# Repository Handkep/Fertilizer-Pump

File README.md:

# Automatic Fertilizer Dispenser

The fertilizer dispenser automatically doses fertilizer concentrates or stock solutions using one or more peristaltic pumps. The amount dispensed depends on the selected recipe and the intended irrigation water volume. After dosing, the pump and outlet tubing are flushed with water to help prevent salt deposits.

**Project status:** In development. The Peristaltic pump is currently in the prototyping phase. PCB design is in progress. The user interface and display are still to be determined.

## How It Works

Each recipe specifies a dose in ml per liter of irrigation water for each fertilizer. The required amount is calculated as follows:

```text
Fertilizer volume [ml] = Water volume [L] × Dose [ml/L]

Example: 10 L of water × 5 ml/L = 50 ml of fertilizer
```

A recipe can contain multiple fertilizers. Each fertilizer has its own separate channel, and the fertilizers are mixed only in the watering can. In the future, the device may support mixing fertilizers, after the pumps, to have a single outlet for the mixed solution. 

## Operation

The planned interface consists of a display and a rotary encoder with a push button:

1. **Set the water volume:** Turn the knob. Each detent increases the selected volume by 1 L.
2. **Confirm the volume:** Press the knob to proceed to recipe selection.
3. **Select a recipe:** Turn the knob to choose the desired recipe.
4. **Start dosing:** Press the knob again to dispense the fertilizer.

the further interface planning is still in progress. The display type has not yet been selected.

## Hardware

| Component | Planned configuration |
| --- | --- |
| Controller | ESP32-S3 |
| Channels | Four positions, initially only two populated with TMC2209 modules |
| Motor drivers | Plug-in TMC2209 StepStick modules |
| Driver control | STEP/DIR/EN and UART |
| Pumps | Custom stepper-driven peristaltic pumps, designed in Onshape |
| Motors | NEMA17 stepper motors |
| User interface | Rotary encoder with push button and a display |
| Display | To be selected: a small OLED or another display type; no seven-segment display |
| Calibration | Individual steps-per-ml calibration for each pump |

## Power and USB

### V1

- Motor and solenoid valve operation requires USB-C PD or a separate 12 V power supply.
- USB-C provides data connectivity and firmware flashing.
- USB alone is intended to power the control electronics, including the ESP32-S3 and user interface. Motors and solenoid valves remain inactive without the 12 V supply. The 12 V supply should not be required for firmware flashing.
- USB Power Delivery is included in V1.

## Fluid Path and Flushing

Each fertilizer channel has a selector valve upstream of the pump:

```mermaid
flowchart LR
    fertilizer["Fertilizer concentrate<br/>or stock solution"] -->|Dosing| valve{"Selector valve"}
    water["Flush water"] -->|Flushing| valve
    valve --> pump(["Peristaltic pump"])
    pump -->|Outlet tubing| can["Watering can"]

    classDef fertilizerStyle fill:#dcfce7,stroke:#15803d,color:#14532d,stroke-width:2px;
    classDef waterStyle fill:#dbeafe,stroke:#2563eb,color:#1e3a8a,stroke-width:2px;
    classDef hardwareStyle fill:#f1f5f9,stroke:#64748b,color:#0f172a,stroke-width:2px;
    classDef outputStyle fill:#fef3c7,stroke:#d97706,color:#78350f,stroke-width:2px;

    class fertilizer fertilizerStyle;
    class water waterStyle;
    class valve,pump hardwareStyle;
    class can outputStyle;
    linkStyle 0 stroke:#15803d,stroke-width:2px;
    linkStyle 1 stroke:#2563eb,stroke-width:2px;
```

V1 will initially use an inexpensive electrically operated two-position solenoid selector valve.

After dosing, the valve switches to water to flush the pump and outlet tubing. The flushing water also flows into the watering can.

The additional flushing water is not included in the fertilizer dose calculation. For the intended use, this extra volume is considered small relative to the uncertainty of measuring the water volume in a watering can.

### Planned for V2

- "peristaltic" selector valve built out of a servo and a 3D-printed part.
    - The servo connector will already be included on the V1 PCB to simplify this future upgrade.

## Development Status

The operating concept, four channel positions with two initially populated motor drivers, and separate fertilizer paths have been defined.

Practical testing is still pending. The display has not yet been selected.

## Future Possibilities

- Release with open-source firmware and noncommercial hardware designs
- A PCB kit or complete DIY kit
- Accompanying project documentation on YouTube

## License

Copyright (c) 2026 Paulus Handke.

- Original firmware: [GPL-3.0-only](LICENSES/GPL-3.0-only.txt), including commercial use and distribution under the GPL.
- Original hardware design files and documentation: [CC BY-NC-SA 4.0](LICENSES/CC-BY-NC-SA-4.0.txt), covering copyright and similar rights.

**Commercial use of the licensed hardware files or documentation, including manufacturing from those files for sale, requires prior written permission**, except as permitted in [LICENSE](LICENSE).
Additional permissions cover paid fabrication for noncommercial end use and freely accessible, monetized project presentations; see [LICENSE](LICENSE) for their scope and conditions.
Third-party material retains its own licenses; see [THIRD_PARTY_NOTICES.md](THIRD_PARTY_NOTICES.md).
For commercial permission, contact Paulus Handke through [repository issues](https://github.com/Handkep/Fertilizer-Pump/issues). An unanswered request is not permission.

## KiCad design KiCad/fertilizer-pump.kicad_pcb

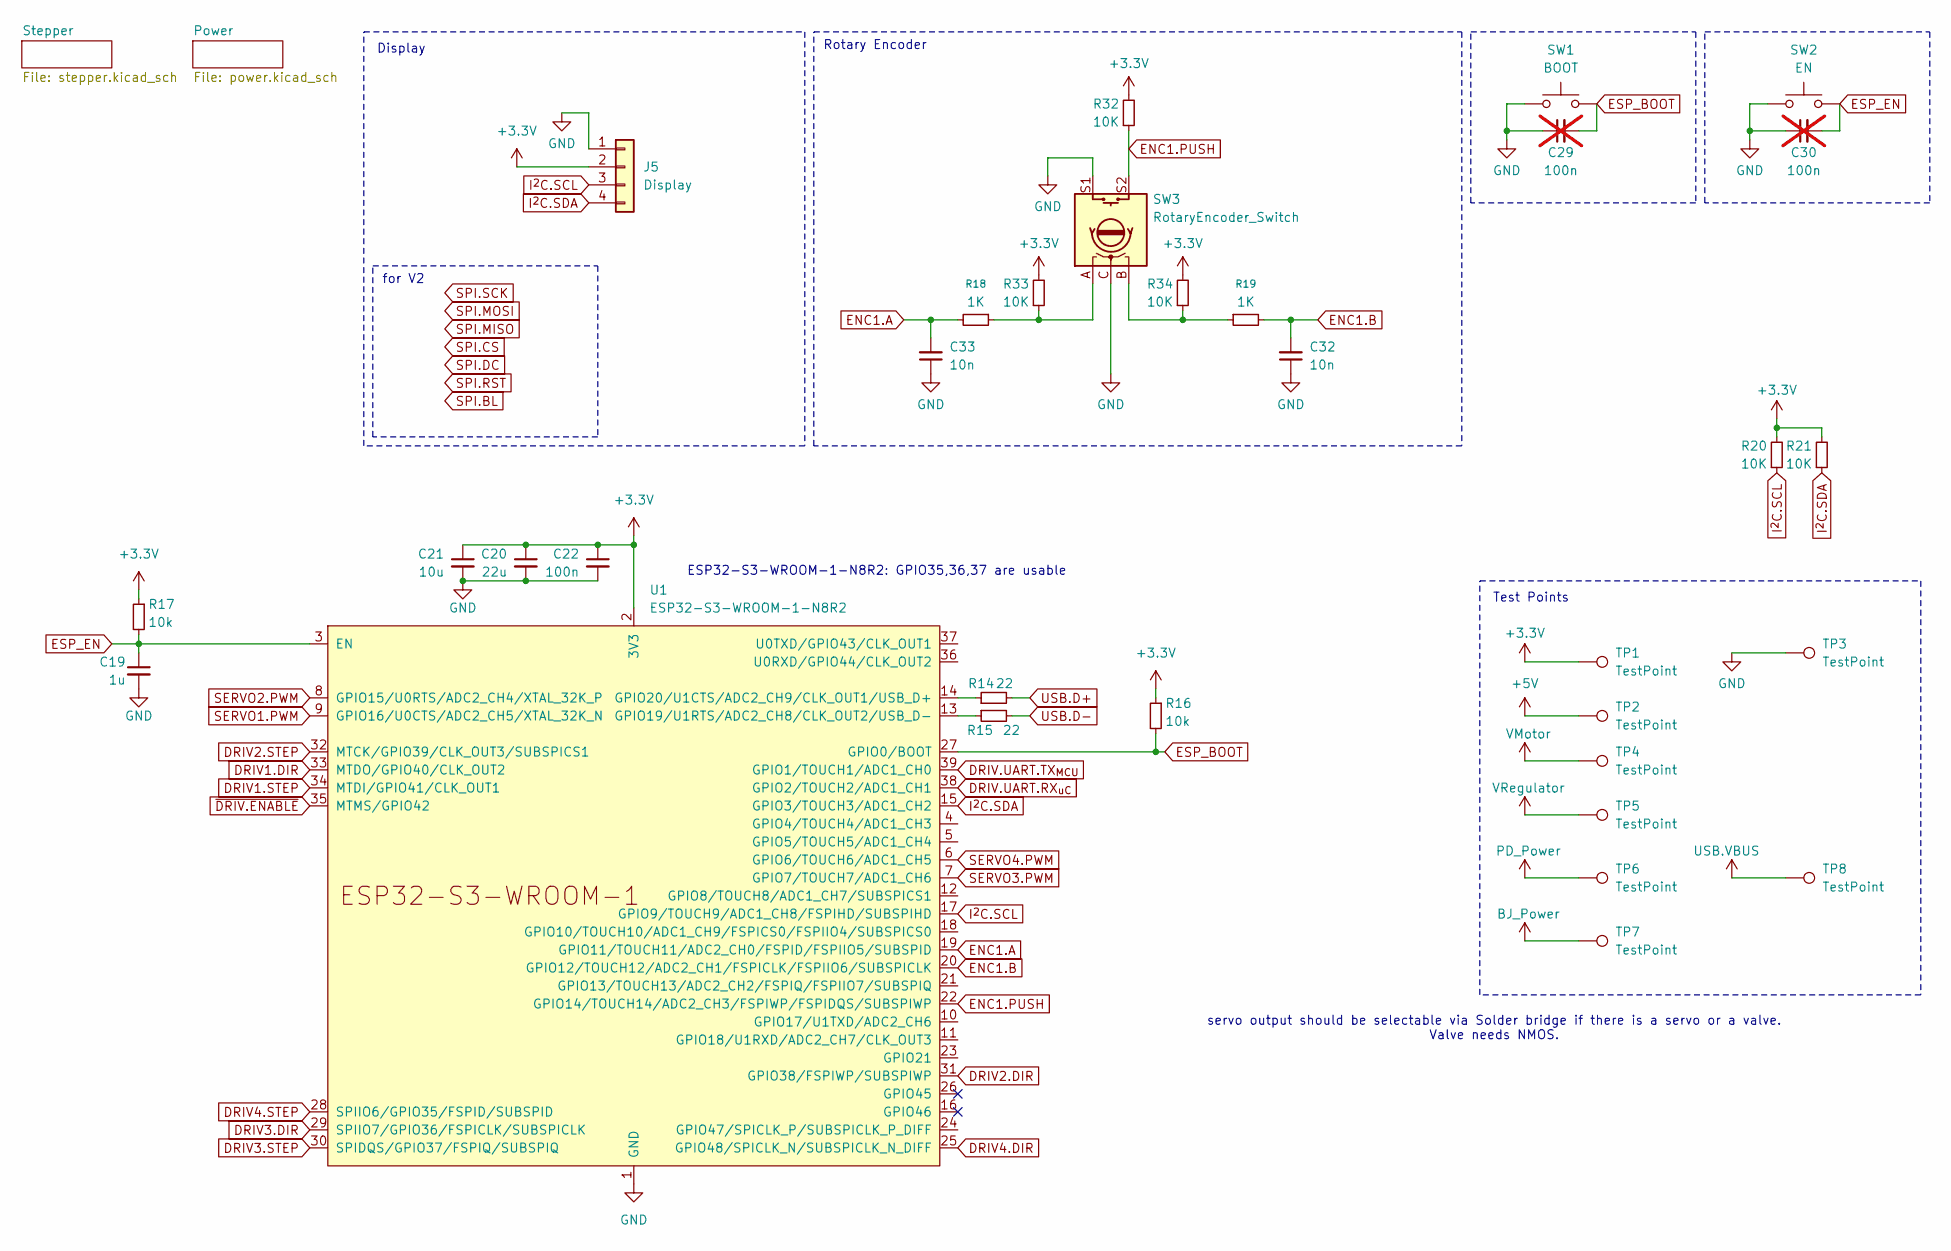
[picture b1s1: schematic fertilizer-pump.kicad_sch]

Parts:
C19: 1u; C_0805_2012Metric_Pad1.18x1.45mm_HandSolder; LCSC C303896
C20: 22u; C_0805_2012Metric_Pad1.18x1.45mm_HandSolder; LCSC C7432777
C21: 10u; C_0805_2012Metric_Pad1.18x1.45mm_HandSolder; LCSC C33546007
C22: 100n; C_0805_2012Metric_Pad1.18x1.45mm_HandSolder; LCSC C5137467
C29, C30: 100n; C_0805_2012Metric_Pad1.18x1.45mm_HandSolder; LCSC C5137467; not fitted
C32, C33: 10n; C_0805_2012Metric_Pad1.18x1.45mm_HandSolder; LCSC C282728
J5: Display; JST_XH_B4B-XH-A_1x04_P2.50mm_Vertical; LCSC C144395
R14, R15: 22; R_0805_2012Metric_Pad1.20x1.40mm_HandSolder; LCSC C56290821
R16, R17: 10k; R_0805_2012Metric_Pad1.20x1.40mm_HandSolder; LCSC C2930231
R18, R19: 1K; R_0805_2012Metric_Pad1.20x1.40mm_HandSolder; LCSC C54921120
R20, R21, R32, R33, R34: 10K; R_0805_2012Metric_Pad1.20x1.40mm_HandSolder; LCSC C2930231
SW1: BOOT; SHOU HAN TS342A2P-WZ; LCSC C557591
SW2: EN; SHOU HAN TS342A2P-WZ; LCSC C557591
SW3: RotaryEncoder_Switch; Rot_Enc_JST_XH_B5B-XH-A_1x05_P2.50mm_Vertical
TP1, TP2, TP3, TP4, TP5, TP6, TP7, TP8: TestPoint; PinHeader_1x01_P2.54mm_Vertical
U1: ESP32-S3-WROOM-1-N8R2; ESP32-S3-WROOM-1; LCSC C2913204

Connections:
+3.3V: C20.1, C21.1, C22.1, J5.2, R16.1, R17.1, R20.2, R21.2, R32.2, R33.2, R34.2, TP1.1 (1_1), U1.2 (3V3); also elsewhere on the board
+5V: TP2.1 (1_1); also elsewhere on the board
BJ_Power: TP7.1 (1_1); also elsewhere on the board
DRIV1.DIR: U1.33 (MTDO/GPIO40/CLK_OUT2); also elsewhere on the board
DRIV1.STEP: U1.34 (MTDI/GPIO41/CLK_OUT1); also elsewhere on the board
DRIV2.DIR: U1.31 (GPIO38/FSPIWP/SUBSPIWP); also elsewhere on the board
DRIV2.STEP: U1.32 (MTCK/GPIO39/CLK_OUT3/SUBSPICS1); also elsewhere on the board
DRIV3.DIR: U1.29 (SPIIO7/GPIO36/FSPICLK/SUBSPICLK); also elsewhere on the board
DRIV3.STEP: U1.30 (SPIDQS/GPIO37/FSPIQ/SUBSPIQ); also elsewhere on the board
DRIV4.DIR: U1.25 (GPIO48/SPICLK_N/SUBSPICLK_N_DIFF); also elsewhere on the board
DRIV4.STEP: U1.28 (SPIIO6/GPIO35/FSPID/SUBSPID); also elsewhere on the board
DRIV.UART: U1.38 (GPIO2/TOUCH2/ADC1_CH1); also elsewhere on the board
DRIV.UART.TX_{MCU}: U1.39 (GPIO1/TOUCH1/ADC1_CH0); also elsewhere on the board
ENC1.A: C33.2, R18.2, U1.19 (GPIO11/TOUCH11/ADC2_CH0/FSPID/FSPIIO5/S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)
ENC1.B: C32.2, R19.2, U1.20 (GPIO12/TOUCH12/ADC2_CH1/FSPICLK/FSPIIO6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)
ENC1.PUSH: R32.1, SW3.S2, U1.22 (GPIO14/TOUCH14/ADC2_CH3/FSPIWP/FSPIDQS/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)
ESP_BOOT: C29.2, R16.2, SW1.2, U1.27 (GPIO0/BOOT)
ESP_EN: C19.1, C30.2, R17.2, SW2.2, U1.3 (EN)
GND: C19.2, C20.2, C21.2, C22.2, C29.1, C30.1, C32.1, C33.1, J5.1, SW1.1, SW2.1, SW3.C, SW3.S1, TP3.1 (1_1), U1.1 (GND), U1.40 (GND), U1.41 (GND); also elsewhere on the board
I^{2}C.SCL: J5.3, R20.1, U1.17 (GPIO9/TOUCH9/ADC1_CH8/FSPIHD/SUBSPIHD); also elsewhere on the board
I^{2}C.SDA: J5.4, R21.1, U1.15 (GPIO3/TOUCH3/ADC1_CH2); also elsewhere on the board
unnamed: R18.1, R33.1, SW3.A
unnamed: R19.1, R34.1, SW3.B
unnamed: R15.1, U1.13 (GPIO19/U1RTS/ADC2_CH8/CLK_OUT2/USB_D-)
unnamed: R14.1, U1.14 (GPIO20/U1CTS/ADC2_CH9/CLK_OUT1/USB_D+)
PD_Power: TP6.1 (1_1); also elsewhere on the board
SERVO1.PWM: U1.9 (GPIO16/U0CTS/ADC2_CH5/XTAL_32K_N); also elsewhere on the board
SERVO2.PWM: U1.8 (GPIO15/U0RTS/ADC2_CH4/XTAL_32K_P); also elsewhere on the board
SERVO3.PWM: U1.7 (GPIO7/TOUCH7/ADC1_CH6); also elsewhere on the board
SERVO4.PWM: U1.6 (GPIO6/TOUCH6/ADC1_CH5); also elsewhere on the board
USB.D+: R14.2; also elsewhere on the board
USB.D-: R15.2; also elsewhere on the board
USB.VBUS: TP8.1 (1_1); also elsewhere on the board
VMotor: TP4.1 (1_1); also elsewhere on the board
VRegulator: TP5.1 (1_1); also elsewhere on the board
~DRIV.ENABLE: U1.35 (MTMS/GPIO42); also elsewhere on the board

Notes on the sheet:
Rotary Encoder
Display
ESP32-S3-WROOM-1-N8R2: GPIO35,36,37 are usable
servo output should be selectable via Solder bridge if there is a servo or a valve. Valve needs NMOS.
for V2
Test Points

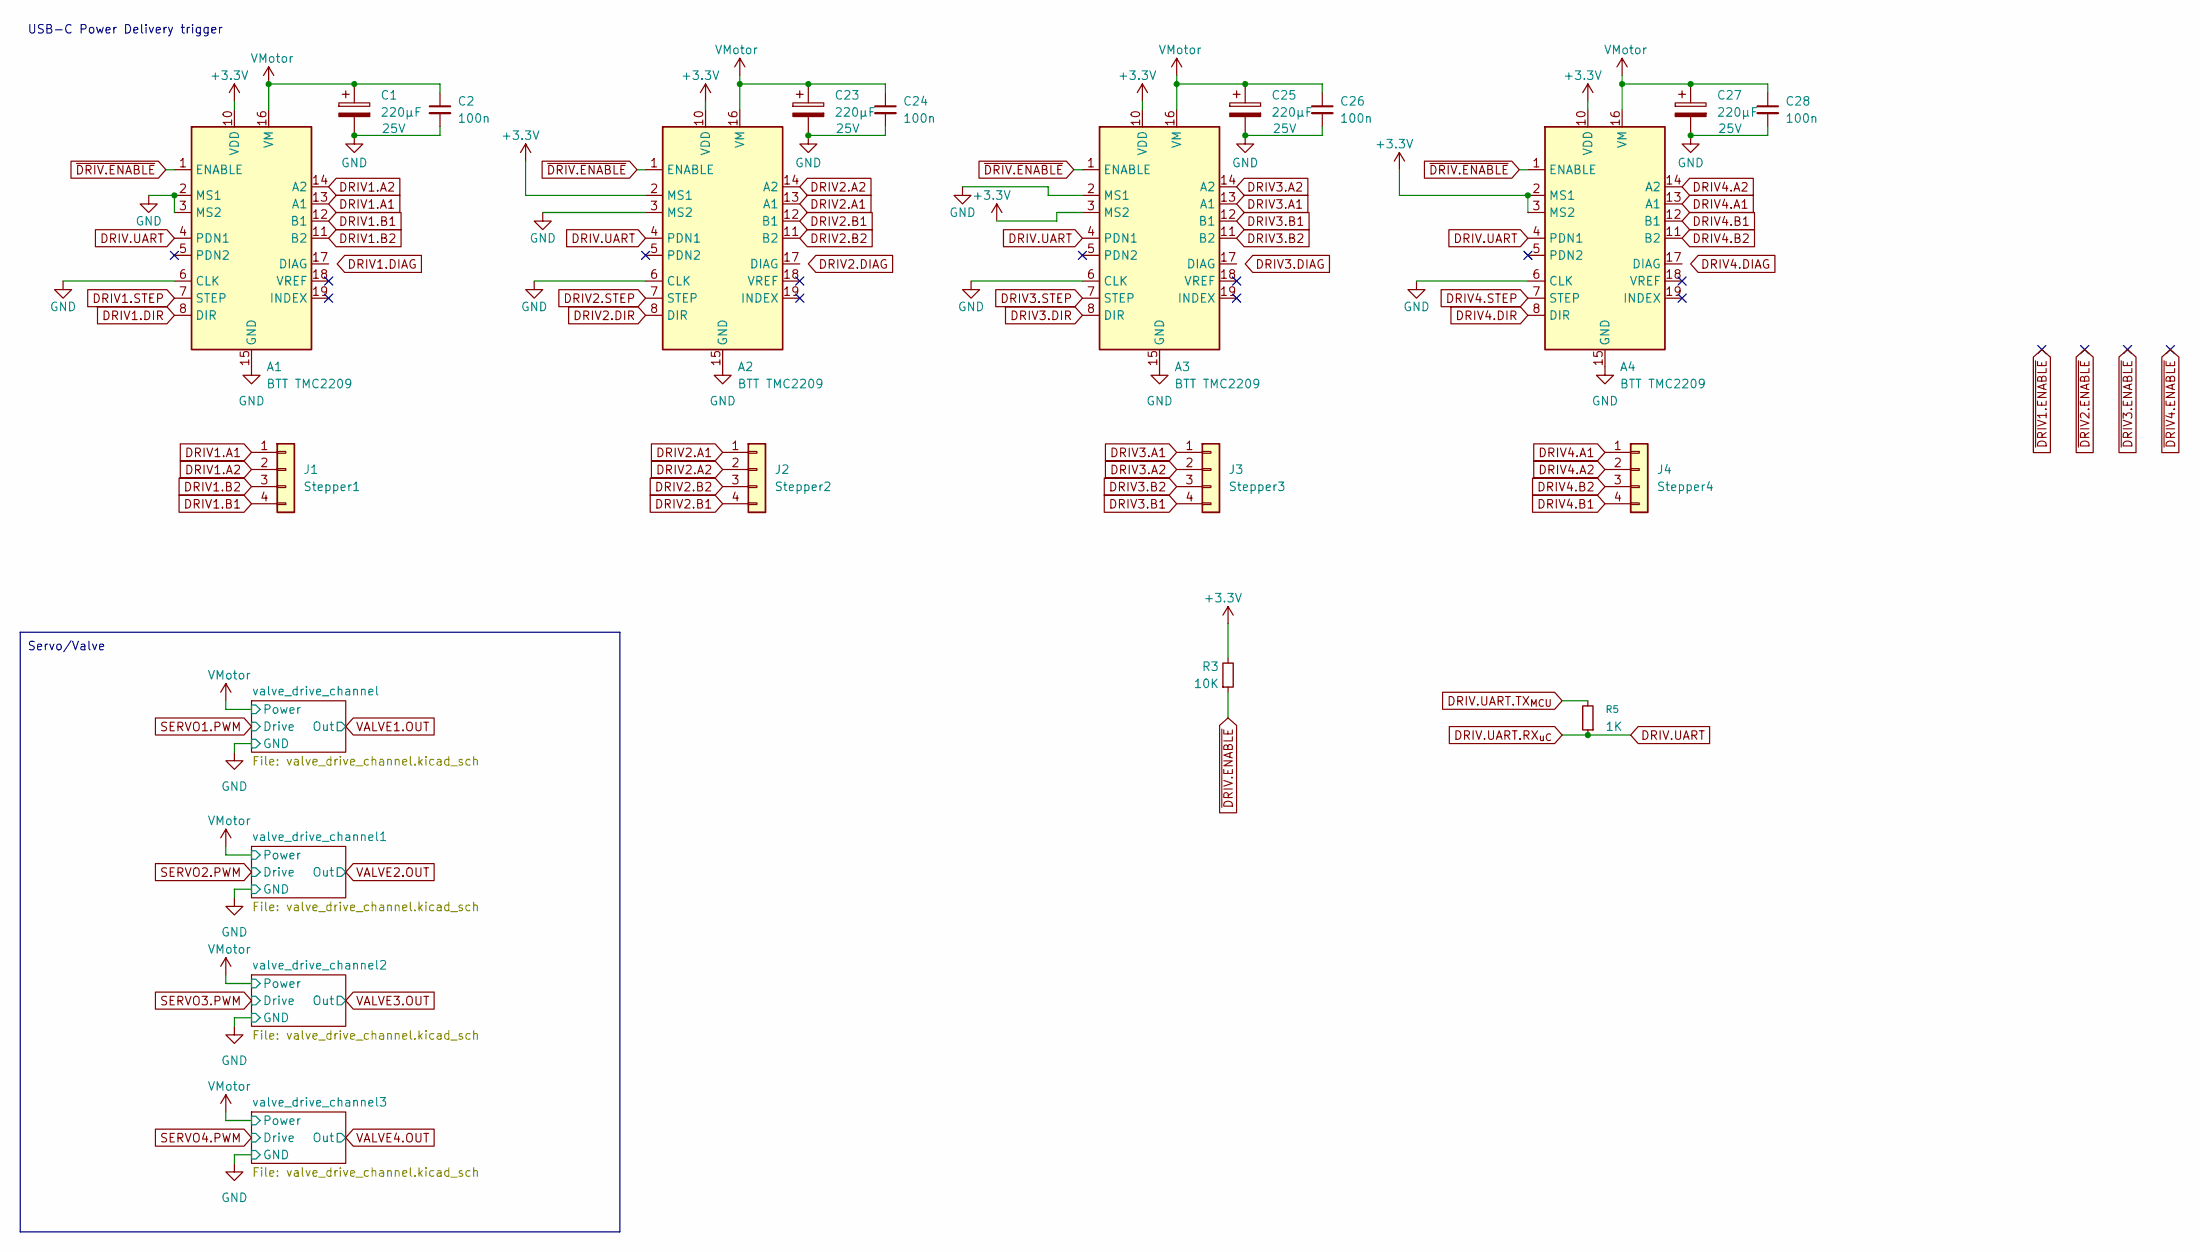
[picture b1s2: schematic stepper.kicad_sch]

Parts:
A1, A2, A3, A4: BTT TMC2209
C1, C23, C25, C27: 220µF; CP_Elec_6.3x7.7; Voltage 25V; LCSC C7471881
C2, C24, C26, C28: 100n; C_0805_2012Metric_Pad1.18x1.45mm_HandSolder; LCSC C48579601
J1: Stepper1; JST_XH_B4B-XH-A_1x04_P2.50mm_Vertical; LCSC C144395
J2: Stepper2; JST_XH_B4B-XH-A_1x04_P2.50mm_Vertical; LCSC C144395
J3: Stepper3; JST_XH_B4B-XH-A_1x04_P2.50mm_Vertical; LCSC C144395
J4: Stepper4; JST_XH_B4B-XH-A_1x04_P2.50mm_Vertical; LCSC C144395
R3: 10K; R_0805_2012Metric_Pad1.20x1.40mm_HandSolder; LCSC C2930231
R5: 1K; R_0805_2012Metric_Pad1.20x1.40mm_HandSolder; LCSC C54921120

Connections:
+3.3V: A1.10 (VDD), A2.2 (MS1), A2.10 (VDD), A3.3 (MS2), A3.10 (VDD), A4.2 (MS1), A4.3 (MS2), A4.10 (VDD), R3.2; also elsewhere on the board
DRIV1.A1: A1.13 (A1), J1.1
DRIV1.A2: A1.14 (A2), J1.2
DRIV1.B1: A1.12 (B1), J1.4
DRIV1.B2: A1.11 (B2), J1.3
DRIV1.DIR: A1.8 (DIR); also elsewhere on the board
DRIV1.STEP: A1.7 (STEP); also elsewhere on the board
DRIV2.A1: A2.13 (A1), J2.1
DRIV2.A2: A2.14 (A2), J2.2
DRIV2.B1: A2.12 (B1), J2.4
DRIV2.B2: A2.11 (B2), J2.3
DRIV2.DIR: A2.8 (DIR); also elsewhere on the board
DRIV2.STEP: A2.7 (STEP); also elsewhere on the board
DRIV3.A1: A3.13 (A1), J3.1
DRIV3.A2: A3.14 (A2), J3.2
DRIV3.B1: A3.12 (B1), J3.4
DRIV3.B2: A3.11 (B2), J3.3
DRIV3.DIR: A3.8 (DIR); also elsewhere on the board
DRIV3.STEP: A3.7 (STEP); also elsewhere on the board
DRIV4.A1: A4.13 (A1), J4.1
DRIV4.A2: A4.14 (A2), J4.2
DRIV4.B1: A4.12 (B1), J4.4
DRIV4.B2: A4.11 (B2), J4.3
DRIV4.DIR: A4.8 (DIR); also elsewhere on the board
DRIV4.STEP: A4.7 (STEP); also elsewhere on the board
DRIV.UART: A1.4 (PDN1), A2.4 (PDN1), A3.4 (PDN1), A4.4 (PDN1), R5.1; also elsewhere on the board
DRIV.UART.TX_{MCU}: R5.2; also elsewhere on the board
GND: A1.2 (MS1), A1.3 (MS2), A1.6 (CLK), A1.9 (GND), A1.15 (GND), A2.3 (MS2), A2.6 (CLK), A2.9 (GND), A2.15 (GND), A3.2 (MS1), A3.6 (CLK), A3.9 (GND), A3.15 (GND), A4.6 (CLK), A4.9 (GND), A4.15 (GND), C1.2, C2.2, C23.2, C24.2, C25.2, C26.2, C27.2, C28.2; also elsewhere on the board
VMotor: A1.16 (VM), A2.16 (VM), A3.16 (VM), A4.16 (VM), C1.1, C2.1, C23.1, C24.1, C25.1, C26.1, C27.1, C28.1; also elsewhere on the board
~DRIV.ENABLE: A1.1 (ENABLE), A2.1 (ENABLE), A3.1 (ENABLE), A4.1 (ENABLE), R3.1; also elsewhere on the board

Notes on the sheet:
USB-C Power Delivery trigger
Servo/Valve

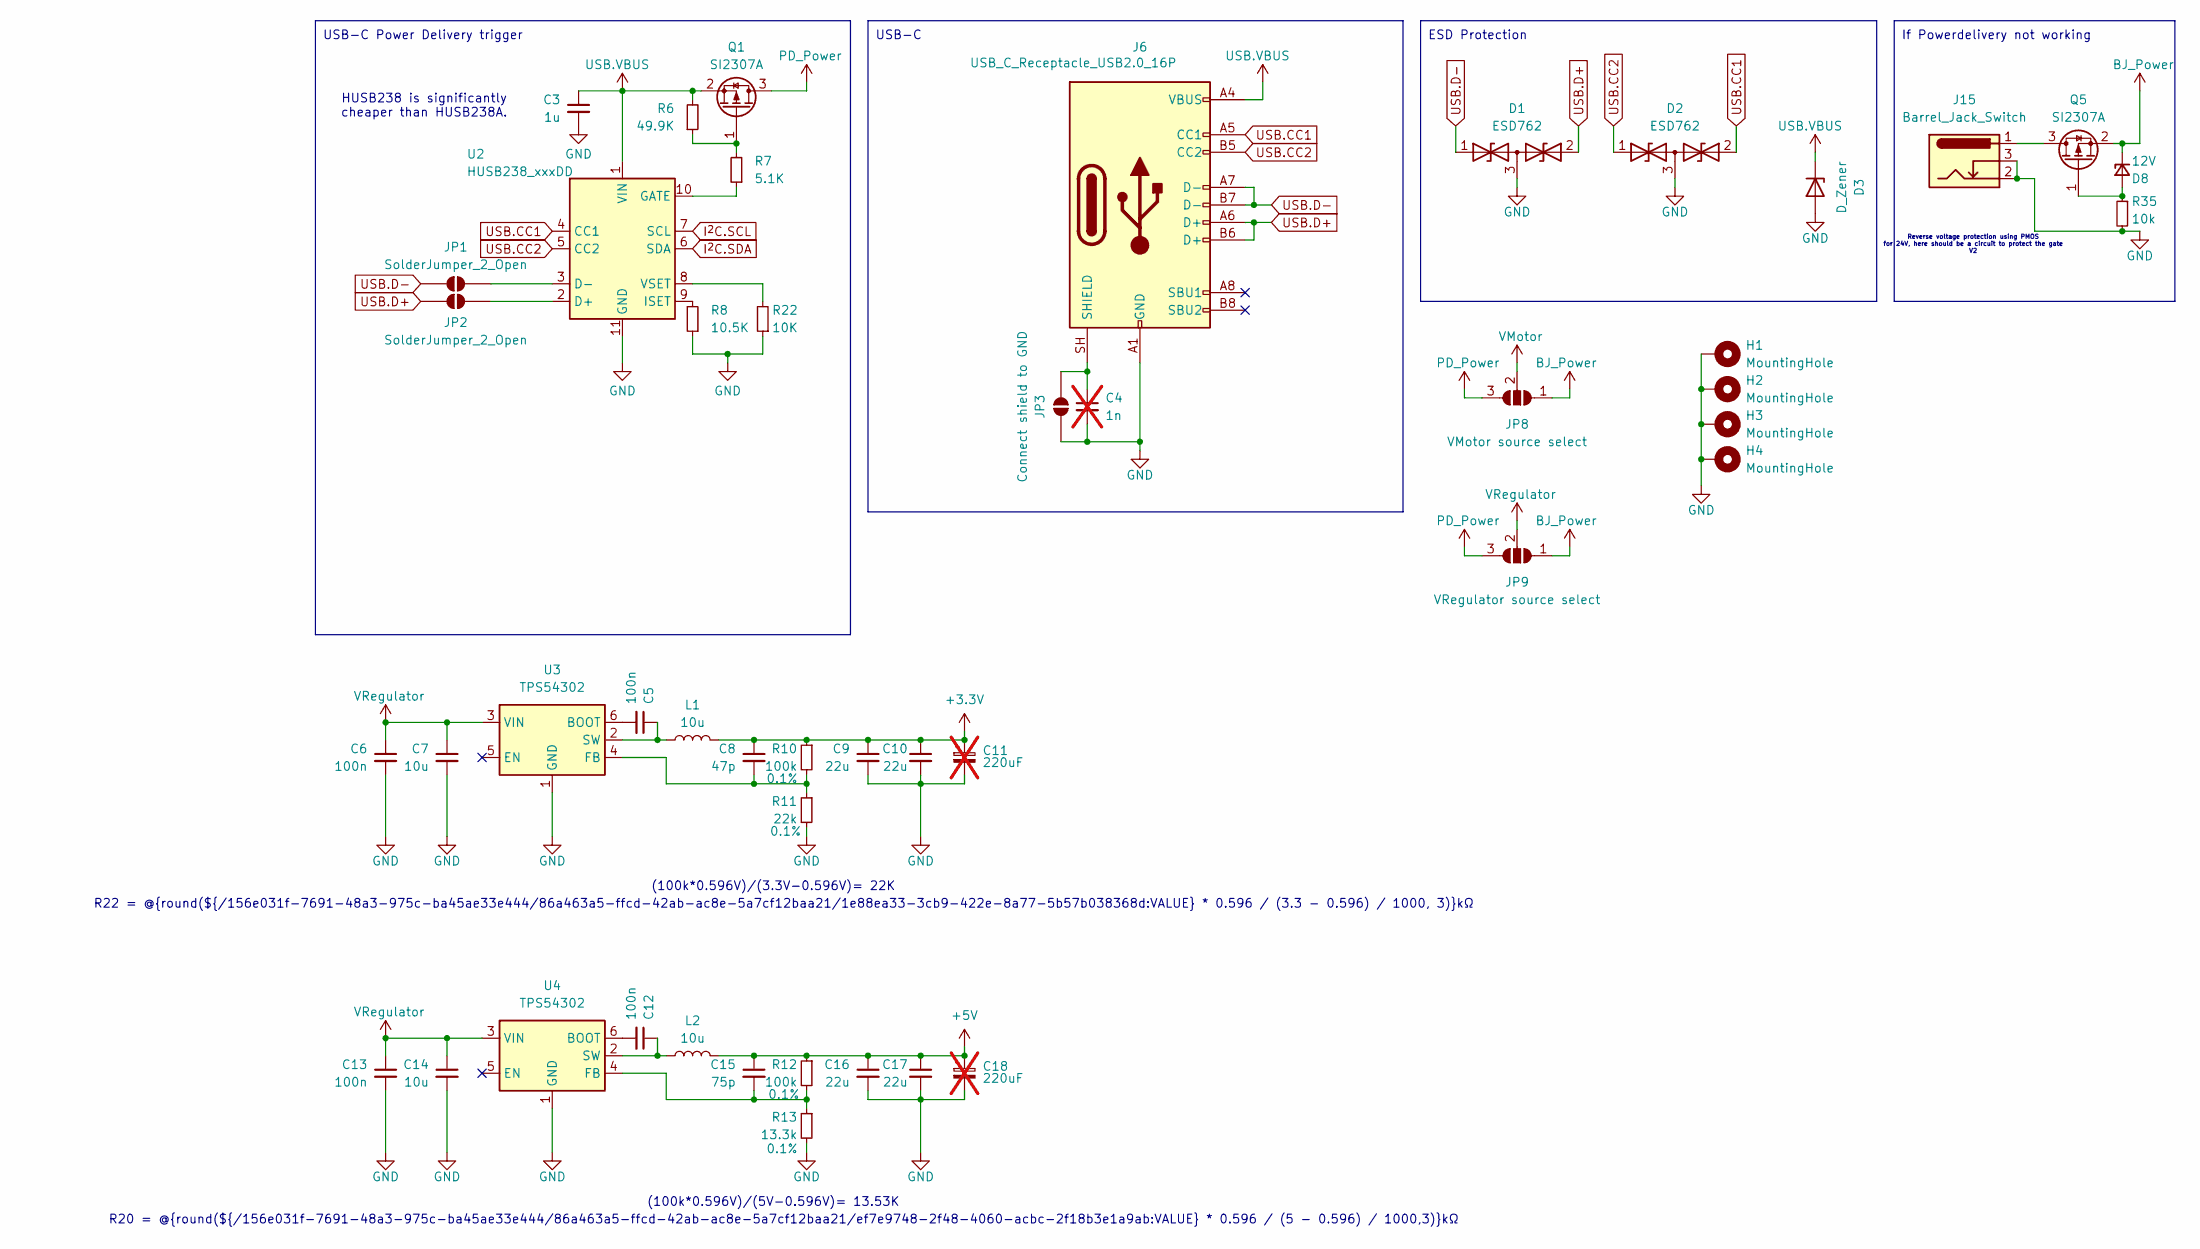
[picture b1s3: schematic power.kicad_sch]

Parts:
C3: 1u; C_0805_2012Metric_Pad1.18x1.45mm_HandSolder; LCSC C89190
C4: 1n; C_0805_2012Metric_Pad1.18x1.45mm_HandSolder; not fitted
C5, C6, C12, C13: 100n; C_0805_2012Metric_Pad1.18x1.45mm_HandSolder; LCSC C5137467
C7, C14: 10u; C_0805_2012Metric_Pad1.18x1.45mm_HandSolder; LCSC C33546007
C8: 47p; C_0603_1608Metric_Pad1.08x0.95mm_HandSolder; LCSC C5137501
C9, C10, C16, C17: 22u; C_0805_2012Metric_Pad1.18x1.45mm_HandSolder; LCSC C7432777
C11, C18: 220uF; CP_Radial_D8.0mm_P3.50mm; LCSC C107639; not fitted
C15: 75p; C_0603_1608Metric_Pad1.08x0.95mm_HandSolder; LCSC C5360822
D1, D2: ESD762; SOT-23_Handsoldering; LCSC C53340942
D3: D_Zener; D_SOD-123FL; LCSC C353298
D8: 12V; D_SOD-123; LCSC C2891780
H1, H2, H3, H4: MountingHole; MountingHole_3.2mm_M3_Pad_Via
J6: USB_C_Receptacle_USB2.0_16P; USB_C_Receptacle_GCT_USB4105-xx-A_16P_TopMnt_Horizontal; LCSC C5178539
J15: Barrel_Jack_Switch; BarrelJack_GCT_DCJ200-10-A_Horizontal; LCSC C22459640
JP1, JP2: SolderJumper_2_Open; SolderJumper-2_P1.3mm_Open_RoundedPad1.0x1.5mm
JP3: Connect shield to GND; SolderJumper-2_P1.3mm_Open_RoundedPad1.0x1.5mm
JP8: VMotor source select; SolderJumper-3_P1.3mm_Open_RoundedPad1.0x1.5mm
JP9: VRegulator source select; SolderJumper-3_P1.3mm_Open_RoundedPad1.0x1.5mm
L1, L2: 10u; L_APV_APH0630; LCSC C5349698
Q1, Q5: SI2307A; SOT-23; LCSC C347490
R6: 49.9K; R_0805_2012Metric_Pad1.20x1.40mm_HandSolder; LCSC C2930203
R7: 5.1K; R_0805_2012Metric_Pad1.20x1.40mm_HandSolder; LCSC C118848
R8: 10.5K; R_0805_2012Metric_Pad1.20x1.40mm_HandSolder; LCSC C40086
R10, R12: 100k; R_0603_1608Metric_Pad0.98x0.95mm_HandSolder; LCSC C51048211
R11: 22k; R_0603_1608Metric_Pad0.98x0.95mm_HandSolder; LCSC C47119950
R13: 13.3k; R_0603_1608Metric_Pad0.98x0.95mm_HandSolder; LCSC C667047
R22: 10K; R_0805_2012Metric_Pad1.20x1.40mm_HandSolder; LCSC C2930231
R35: 10k; R_0805_2012Metric_Pad1.20x1.40mm_HandSolder; LCSC C2930231
U2: HUSB238_xxxDD; WDFN-10-1EP_3x3mm_P0.5mm_EP1.8x2.5mm_ThermalVias; LCSC C7471904
U3, U4: TPS54302; SOT-23-6; LCSC C311983

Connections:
+3.3V: C8.1, C9.1, C10.1, C11.1, L1.2, R10.1; also elsewhere on the board
+5V: C15.1, C16.1, C17.1, C18.1, L2.2, R12.1; also elsewhere on the board
BJ_Power: D8.1 (K), JP8.1 (A), JP9.1 (A), Q5.2 (S); also elsewhere on the board
GND: C3.2, C4.2, C6.2, C7.2, C9.2, C10.2, C11.2, C13.2, C14.2, C16.2, C17.2, C18.2, D1.3 (common), D2.3 (common), D3.2 (A), H1.1 (1_1), H2.1 (1_1), H3.1 (1_1), H4.1 (1_1), J6.A1 (GND), J6.A12 (GND), J6.B1 (GND), J6.B12 (GND), J15.2, J15.3, JP3.1 (A), R8.1, R11.2, R13.2, R22.1, R35.2, U2.11 (GND), U3.1 (GND), U4.1 (GND); also elsewhere on the board
I^{2}C.SCL: U2.7 (SCL); also elsewhere on the board
I^{2}C.SDA: U2.6 (SDA); also elsewhere on the board
unnamed: D8.2 (A), Q5.1 (G), R35.1
unnamed: C4.1, J6.SH (SHIELD), JP3.2 (B)
unnamed: JP1.2 (B), U2.3 (D-)
unnamed: JP2.2 (B), U2.2 (D+)
unnamed: Q1.1 (G), R6.1, R7.2
unnamed: J15.1, Q5.3 (D)
unnamed: R7.1, U2.10 (GATE)
unnamed: R8.2, U2.9 (ISET)
unnamed: R22.2, U2.8 (VSET)
unnamed: C5.2, U3.6 (BOOT)
unnamed: C8.2, R10.2, R11.1, U3.4 (FB)
unnamed: C5.1, L1.1, U3.2 (SW)
unnamed: C12.2, U4.6 (BOOT)
unnamed: C15.2, R12.2, R13.1, U4.4 (FB)
unnamed: C12.1, L2.1, U4.2 (SW)
PD_Power: JP8.3 (B), JP9.3 (B), Q1.3 (D); also elsewhere on the board
USB.CC1: D2.2 (A2), J6.A5 (CC1), U2.4 (CC1)
USB.CC2: D2.1 (A1), J6.B5 (CC2), U2.5 (CC2)
USB.D+: D1.2 (A2), J6.A6 (D+), J6.B6 (D+), JP2.1 (A); also elsewhere on the board
USB.D-: D1.1 (A1), J6.A7 (D-), J6.B7 (D-), JP1.1 (A); also elsewhere on the board
USB.VBUS: C3.1, D3.1 (K), J6.A4 (VBUS), J6.A9 (VBUS), J6.B4 (VBUS), J6.B9 (VBUS), Q1.2 (S), R6.2, U2.1 (VIN); also elsewhere on the board
VMotor: JP8.2 (C); also elsewhere on the board
VRegulator: C6.1, C7.1, C13.1, C14.1, JP9.2 (C), U3.3 (VIN), U4.3 (VIN); also elsewhere on the board

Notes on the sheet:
If Powerdelivery not working
USB-C Power Delivery trigger
Reverse voltage protection using PMOS for 24V, here should be a circuit to protect the gate V2
ESD Protection
HUSB238 is significantly cheaper than HUSB238A.
R22 = @{round(${/156e031f-7691-48a3-975c-ba45ae33e444/86a463a5-ffcd-42ab-ac8e-5a7cf12baa21/1e88ea33-3cb9-422e-8a77-5b57b038368d:VALUE} * 0.596 / (3.3 - 0.596) / 1000, 3)}kΩ
(100k*0.596V)/(5V-0.596V)= 13.53K
(100k*0.596V)/(3.3V-0.596V)= 22K
USB-C
R20 = @{round(${/156e031f-7691-48a3-975c-ba45ae33e444/86a463a5-ffcd-42ab-ac8e-5a7cf12baa21/ef7e9748-2f48-4060-acbc-2f18b3e1a9ab:VALUE} * 0.596 / (5 - 0.596) / 1000,3)}kΩ

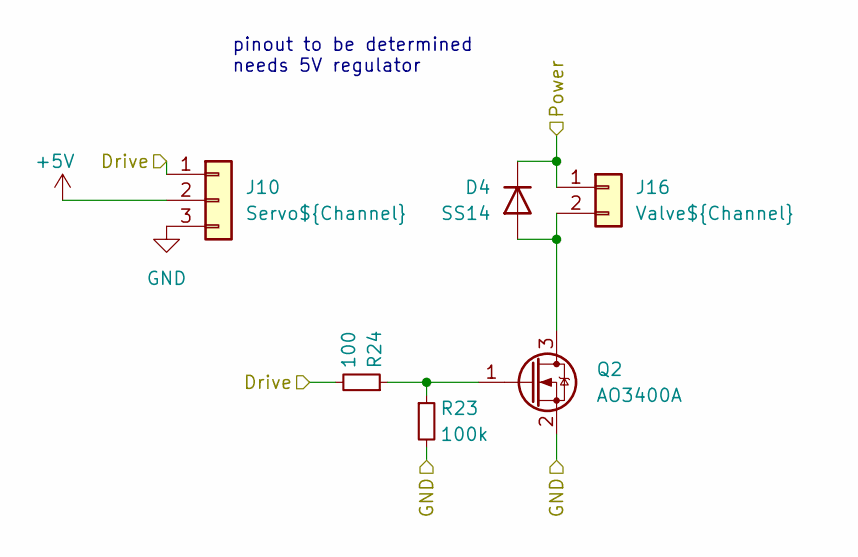
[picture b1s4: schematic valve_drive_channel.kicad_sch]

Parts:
D4: SS14; D_SMA_Handsoldering; LCSC C2480
J10: Servo${Channel}; JST_XH_B3B-XH-A_1x03_P2.50mm_Vertical; LCSC C144394
J16: Valve${Channel}; JST_XH_B2B-XH-A_1x02_P2.50mm_Vertical; LCSC C158012
Q2: AO3400A; SOT-23; LCSC C347475
R23: 100k; R_0805_2012Metric_Pad1.20x1.40mm_HandSolder; LCSC C3017875
R24: 100; R_0805_2012Metric_Pad1.20x1.40mm_HandSolder; LCSC C2907294

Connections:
+5V: J10.2; also elsewhere on the board
GND: J10.3, Q2.2 (S), R23.2; also elsewhere on the board
unnamed: D4.2 (A), J16.2, Q2.3 (D)
unnamed: Q2.1 (G), R23.1, R24.1
SERVO1.PWM: J10.1, R24.2; also elsewhere on the board
VMotor: D4.1 (K), J16.1; also elsewhere on the board

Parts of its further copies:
D5, D6, D7: SS14; D_SMA_Handsoldering; LCSC C2480
Q3, Q4, Q9: AO3400A; SOT-23; LCSC C347475
R25, R27, R29: 100; R_0805_2012Metric_Pad1.20x1.40mm_HandSolder; LCSC C2907294
R26, R28, R30: 100k; R_0805_2012Metric_Pad1.20x1.40mm_HandSolder; LCSC C3017875

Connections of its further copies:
GND: Q3.2 (S), Q4.2 (S), Q9.2 (S), R26.2, R28.2, R30.2; also elsewhere on the board
unnamed 38: D5.2 (A), Q3.3 (D); also elsewhere on the board
unnamed 39: D6.2 (A), Q4.3 (D); also elsewhere on the board
unnamed 40: D7.2 (A), Q9.3 (D); also elsewhere on the board
unnamed: Q3.1 (G), R25.1, R26.1
unnamed: Q4.1 (G), R27.1, R28.1
unnamed: Q9.1 (G), R29.1, R30.1
SERVO2.PWM: R25.2; also elsewhere on the board
SERVO3.PWM: R27.2; also elsewhere on the board
SERVO4.PWM: R29.2; also elsewhere on the board
VMotor: D5.1 (K), D6.1 (K), D7.1 (K); also elsewhere on the board

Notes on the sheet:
pinout to be determined needs 5V regulator

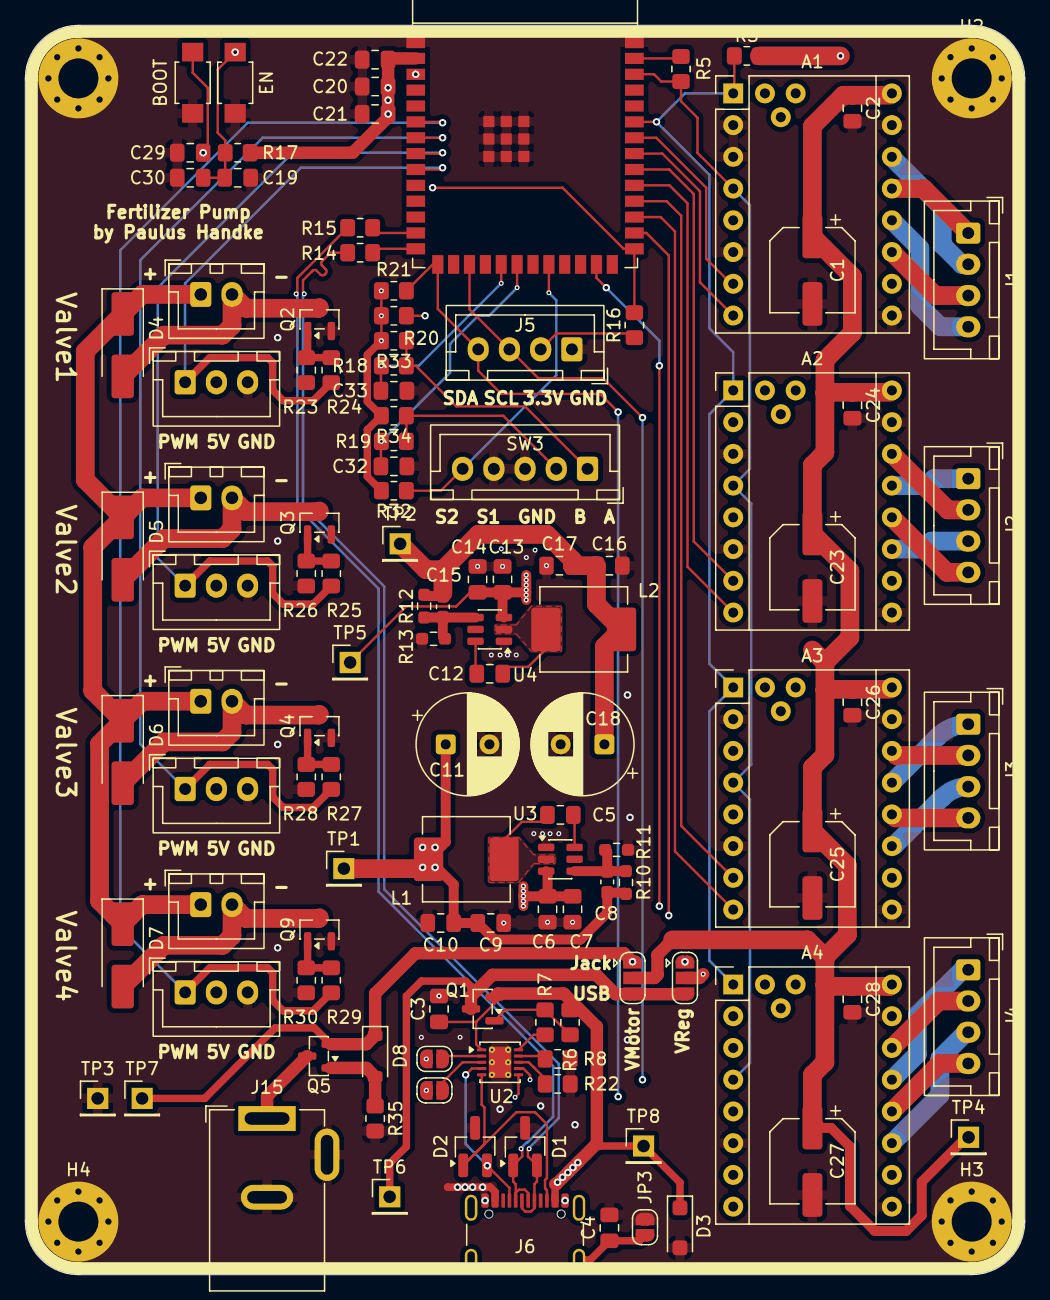
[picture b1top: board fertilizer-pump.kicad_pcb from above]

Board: 4 copper layers, 80.0 x 100.0 mm, 121 parts (0 on the bottom side), 77 nets.

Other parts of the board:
J11: Servo2; JST_XH_B3B-XH-A_1x03_P2.50mm_Vertical
J17: Valve2; JST_XH_B2B-XH-A_1x02_P2.50mm_Vertical
J18: Valve3; JST_XH_B2B-XH-A_1x02_P2.50mm_Vertical
J19: Valve4; JST_XH_B2B-XH-A_1x02_P2.50mm_Vertical
J20: Servo3; JST_XH_B3B-XH-A_1x03_P2.50mm_Vertical
J21: Servo4; JST_XH_B3B-XH-A_1x03_P2.50mm_Vertical

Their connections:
+5V: J11.2, J20.2, J21.2; also elsewhere on the board
GND: J11.3, J20.3, J21.3; also elsewhere on the board
unnamed 38: J17.2; also elsewhere on the board
unnamed 39: J18.2; also elsewhere on the board
unnamed 40: J19.2; also elsewhere on the board
SERVO2.PWM: J11.1; also elsewhere on the board
SERVO3.PWM: J20.1; also elsewhere on the board
SERVO4.PWM: J21.1; also elsewhere on the board
VMotor: J17.1, J18.1, J19.1; also elsewhere on the board
